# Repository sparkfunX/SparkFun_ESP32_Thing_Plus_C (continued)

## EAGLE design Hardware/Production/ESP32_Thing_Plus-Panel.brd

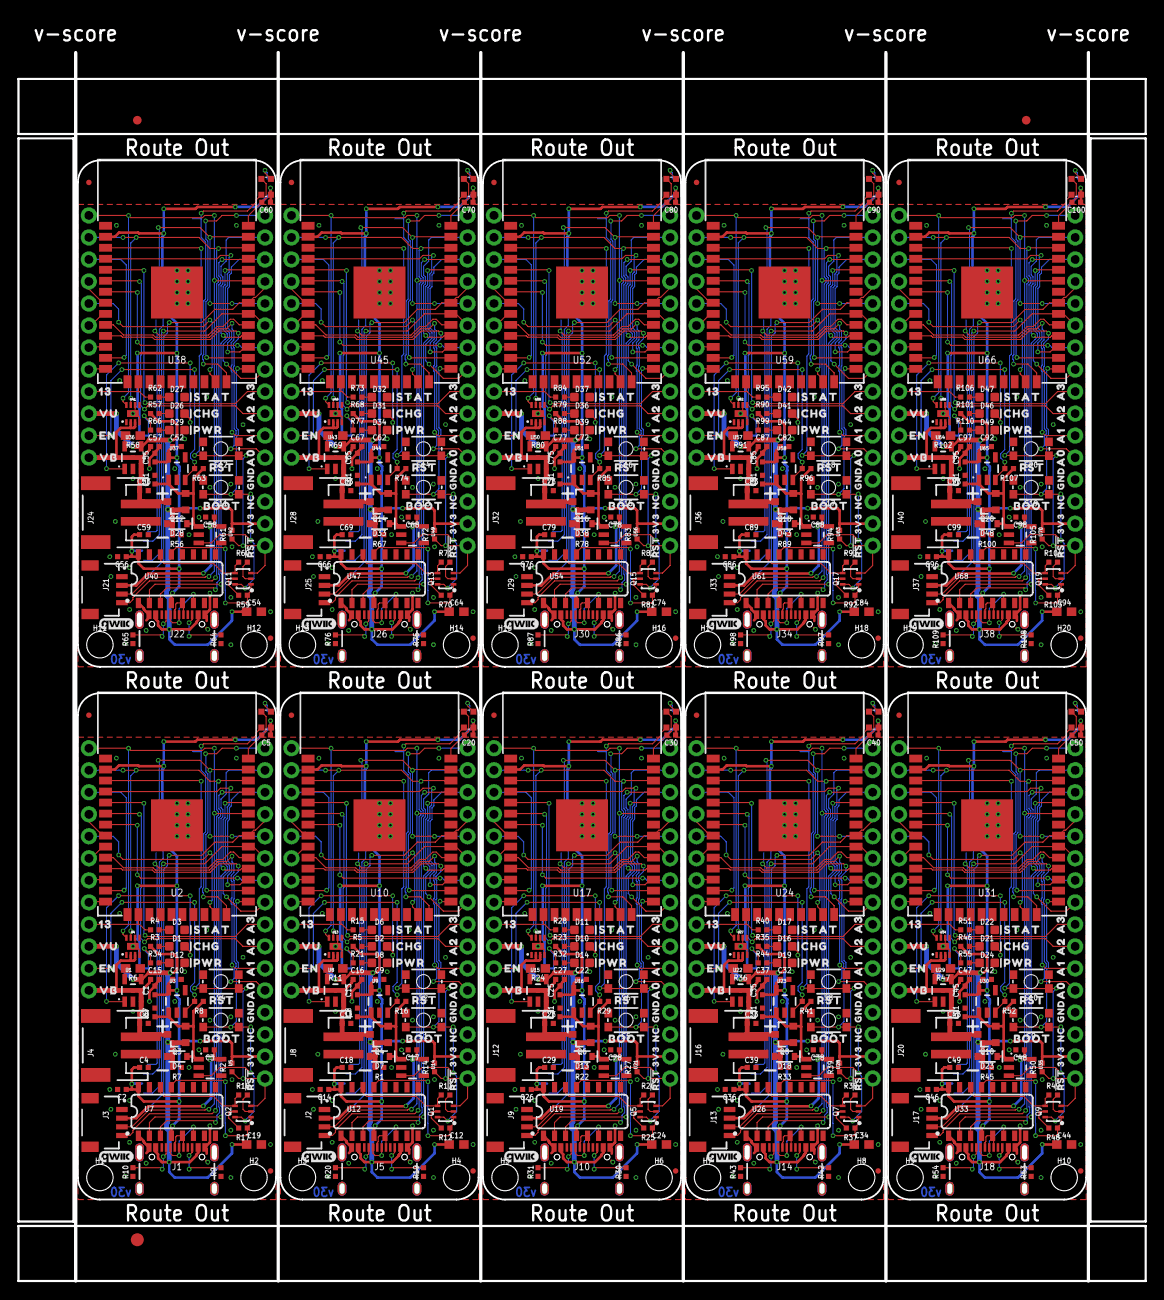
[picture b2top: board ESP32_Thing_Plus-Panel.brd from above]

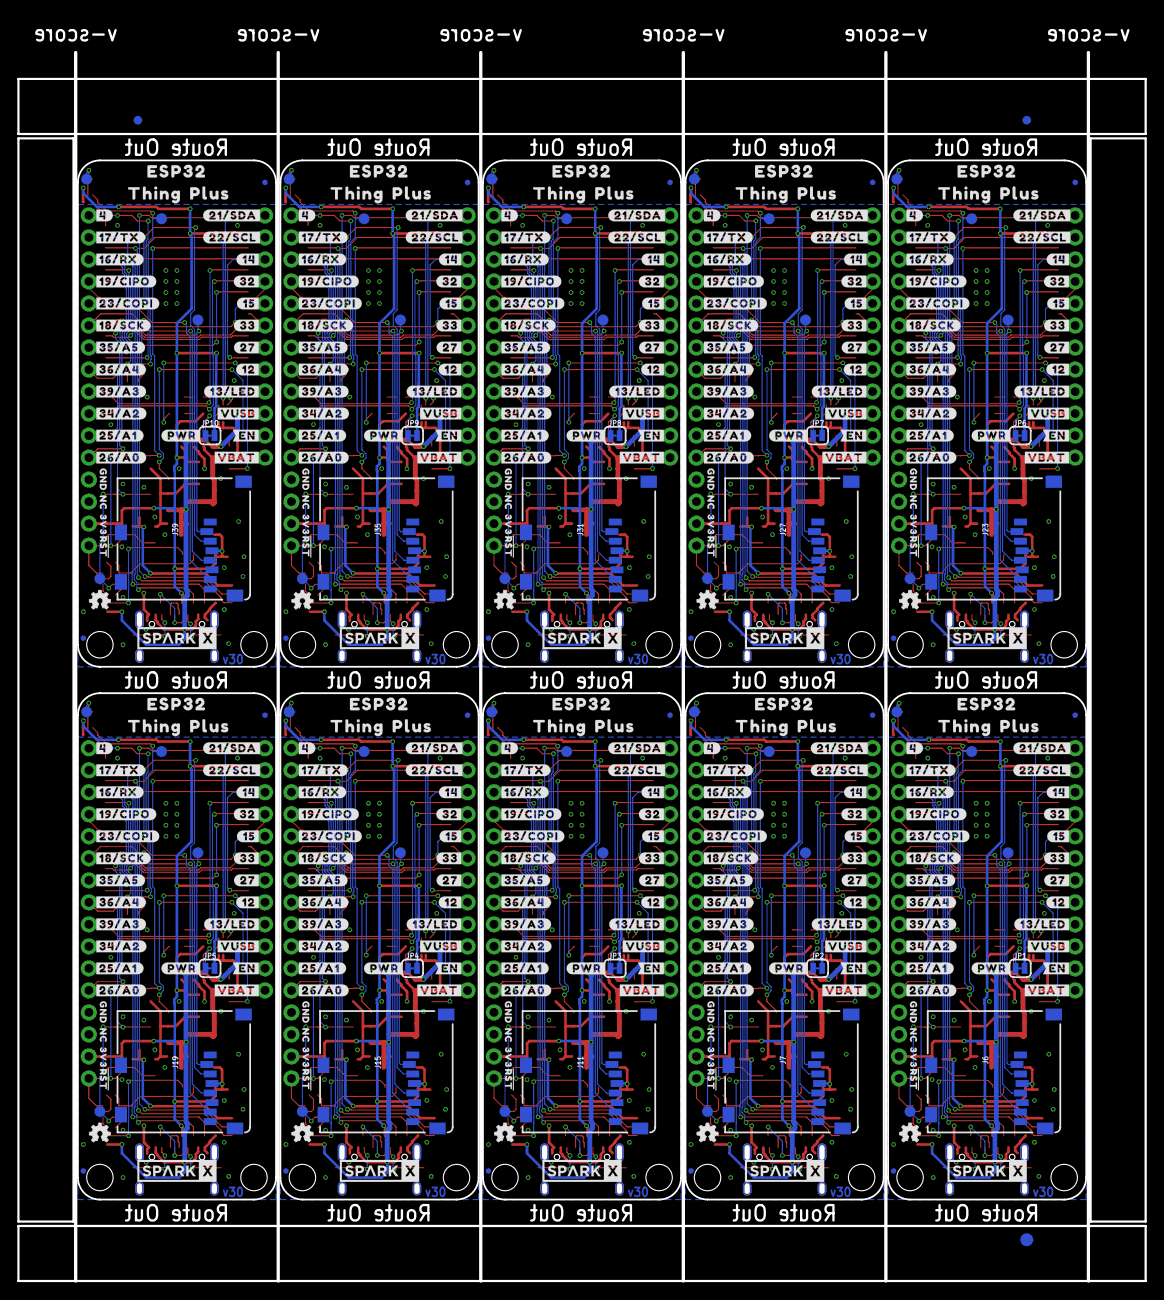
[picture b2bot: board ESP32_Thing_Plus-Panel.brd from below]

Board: 2 copper layers, 129.7 x 145.4 mm, 1046 parts (423 on the bottom side), 490 nets.

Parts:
C1, C13, C25, C35, C45, C55, C65, C75, C85, C95: 10uF; 0402-TIGHT
C2, C4, C5, C14, C15, C16, C18, C20, C26, C27, C29, C30, C36, C37, C39, C40, C46, C47, C49, C50, C56, C57, C59, C60, C66, C67, C69, C70, C76, C77, C79, C80, C86, C87, C89, C90, C96, C97, C99, C100: 0.1uF; 0402-TIGHT
C3, C7, C8, C9, C10, C17, C21, C22, C28, C31, C32, C38, C41, C42, C48, C51, C52, C58, C61, C62, C68, C71, C72, C78, C81, C82, C88, C91, C92, C98: 1.0uF; 0402-TIGHT
C6, C11, C23, C33, C43, C53, C63, C73, C83, C93: 4.7uF; 0402-TIGHT
C12, C19, C24, C34, C44, C54, C64, C74, C84, C94: 4.7uF; 0603
D1, D2, D10, D16, D21, D26, D31, D36, D41, D46: Yellow; LED-0603
D3, D6, D11, D17, D22, D27, D32, D37, D42, D47: BLUE; LED-0603
D4, D7, D13, D18, D23, D28, D33, D38, D43, D48: 3A/10V/280mV; SOD-323
D5, D9, D15, D20, D25, D30, D35, D40, D45, D50: WS2812; WS2812-2020
D8, D12, D14, D19, D24, D29, D34, D39, D44, D49: RED; LED-0603
E$1, E$2, E$3, E$4: FIDUCIAL-1X2
E$5, E$6: FIDUCIAL-1.5X3
FD1, FD2, FD3, FD4, FD5, FD6, FD7, FD8, FD9, FD10, FD11, FD12, FD13, FD14, FD15, FD16, FD17, FD18, FD19, FD20, FD21, FD22, FD23, FD24, FD25, FD26, FD27, FD28, FD29, FD30, FD31, FD32, FD33, FD34, FD35, FD36, FD37, FD38, FD39, FD40: FIDUCIALUFIDUCIAL; FIDUCIAL-MICRO
H1, H2, H3, H4, H5, H6, H7, H8, H9, H10, H11, H12, H13, H14, H15, H16, H17, H18, H19, H20: STAND-OFFTIGHT; STAND-OFF-TIGHT
J1, J5, J10, J14, J18, J22, J26, J30, J34, J38: USB-C-16P-2LAYER-PADS
J2, J3, J9, J13, J17, J21, J25, J29, J33, J37: QWIIC_RIGHT_ANGLE; JST04_1MM_RA
J4, J8, J12, J16, J20, J24, J28, J32, J36, J40: JST-2-SMD
J6, J7, J11, J15, J19, J23, J27, J31, J35, J39: microSD; MICRO-SD-SOCKET
JP1, JP2, JP3, JP4, JP5, JP6, JP7, JP8, JP9, JP10: SMT-JUMPER_2_NC_TRACE_SILK
LOGO1, LOGO2, LOGO5, LOGO7, LOGO9, LOGO11, LOGO13, LOGO15, LOGO17, LOGO19: OSHW-LOGOMINI; OSHW-LOGO-MINI
LOGO3, LOGO4, LOGO6, LOGO8, LOGO10, LOGO12, LOGO14, LOGO16, LOGO18, LOGO20: QWIIC_LOGO_4MM; QWIIC_4MM
Q1, Q2, Q5, Q7, Q9, Q11, Q13, Q15, Q17, Q19: MBT3904DW1T1; SC70-6
Q3, Q4, Q6, Q8, Q10, Q12, Q14, Q16, Q18, Q20: 20V/4.2A/52mΩ/1.4W; SOT23-3
R1, R2, R7, R8, R12, R13, R14, R16, R17, R18, R22, R25, R26, R27, R29, R33, R37, R38, R39, R41, R45, R48, R49, R50, R52, R56, R59, R60, R61, R63, R67, R70, R71, R72, R74, R78, R81, R82, R83, R85, R89, R92, R93, R94, R96, R100, R103, R104, R105, R107: 10k; 0402-TIGHT
R3, R4, R5, R15, R21, R23, R28, R32, R34, R35, R40, R44, R46, R51, R55, R57, R62, R66, R68, R73, R77, R79, R84, R88, R90, R95, R99, R101, R106, R110: 1k; 0402-TIGHT
R6, R11, R24, R36, R47, R58, R69, R80, R91, R102: 2.0k; 0603
R9, R10, R19, R20, R30, R31, R42, R43, R53, R54, R64, R65, R75, R76, R86, R87, R97, R98, R108, R109: 5.1k; 0402-TIGHT
S1, S3, S5, S7, S9, S11, S13, S15, S17, S19: Boot; TACTILE_SWITCH_SMD_4.6X2.8MM
S2, S4, S6, S8, S10, S12, S14, S16, S18, S20: Reset; TACTILE_SWITCH_SMD_4.6X2.8MM
TP1, TP2, TP3, TP4, TP5, TP6, TP7, TP8, TP9, TP10, TP11, TP12, TP13, TP14, TP15, TP16, TP17, TP18, TP19, TP20, TP21, TP22, TP23, TP24, TP25, TP26, TP27, TP28, TP29, TP30, TP31, TP32, TP33, TP34, TP35, TP36, TP37, TP38, TP39, TP40: PAD.03X.05
U1, U8, U15, U22, U29, U36, U43, U50, U57, U64: MCP73831; SOT23-5
U2, U10, U17, U24, U31, U38, U45, U52, U59, U66: ESP-WROOM-32NARROW; ESP-WROOM-32-NARROW
U3, U5, U9, U14, U16, U21, U23, U28, U30, U35, U37, U42, U44, U49, U51, U56, U58, U63, U65, U70: AP2112K-3.3; SOT23-5
U4, U13, U20, U27, U34, U41, U48, U55, U62, U69: MAX17048; DFN-8
U6, U11, U18, U25, U32, U39, U46, U53, U60, U67: THINGPLUS_LOGICAL; THINGPLUS_FOOTPRINT
U7, U12, U19, U26, U33, U40, U47, U54, U61, U68: CH340C; SO016
U$1, U$55, U$150, U$200, U$250, U$300, U$350, U$400, U$450, U$500: SPARKX-LOGO4; SPARKX-MEDIUM
U$2, U$24, U$58, U$151, U$201, U$251, U$301, U$351, U$401, U$451: CHG1
U$3, U$25, U$59, U$152, U$202, U$252, U$302, U$352, U$402, U$452: PWR2
U$4, U$26, U$60, U$153, U$203, U$253, U$303, U$353, U$403, U$453: STAT0
U$5, U$61, U$68, U$154, U$204, U$254, U$304, U$354, U$404, U$454: A03
U$6, U$63, U$69, U$155, U$205, U$255, U$305, U$355, U$405, U$455: A12
U$7, U$64, U$70, U$156, U$206, U$256, U$306, U$356, U$406, U$456: A21
U$8, U$65, U$71, U$157, U$207, U$257, U$307, U$357, U$407, U$457: A30
U$9, U$66, U$74, U$158, U$208, U$258, U$308, U$358, U$408, U$458: EN3
U$10, U$67, U$77, U$159, U$209, U$259, U$309, U$359, U$409, U$459: 130
U$11, U$78, U$110, U$160, U$210, U$260, U$310, U$360, U$410, U$460: BOOT0
U$12, U$50, U$79, U$109, U$111, U$145, U$161, U$195, U$211, U$245, U$261, U$295, U$311, U$345, U$361, U$395, U$411, U$445, U$461, U$495: #RST#0
U$13, U$80, U$112, U$162, U$212, U$262, U$312, U$362, U$412, U$462: RST0
U$14, U$73, U$113, U$163, U$213, U$263, U$313, U$363, U$413, U$463: VB1
U$15, U$76, U$114, U$164, U$214, U$264, U$314, U$364, U$414, U$464: VU0
U$16, U$23, U$49, U$108, U$115, U$144, U$165, U$194, U$215, U$244, U$265, U$294, U$315, U$344, U$365, U$394, U$415, U$444, U$465, U$494: 3V30
U$17, U$57, U$116, U$166, U$216, U$266, U$316, U$366, U$416, U$466: #4#0
U$18, U$62, U$117, U$167, U$217, U$267, U$317, U$367, U$417, U$467: #23#COPI#0
U$19, U$72, U$118, U$168, U$218, U$268, U$318, U$368, U$418, U$468: #17#TX#0
U$20, U$81, U$119, U$169, U$219, U$269, U$319, U$369, U$419, U$469: #16#RX#0
U$21, U$82, U$120, U$170, U$220, U$270, U$320, U$370, U$420, U$470: #19#CIPO#0
U$22, U$83, U$121, U$171, U$221, U$271, U$321, U$371, U$421, U$471: #18#SCK#0
U$27, U$84, U$122, U$172, U$222, U$272, U$322, U$372, U$422, U$472: #35#A5#0
U$28, U$85, U$123, U$173, U$223, U$273, U$323, U$373, U$423, U$473: #36#A4#0
U$29, U$86, U$124, U$174, U$224, U$274, U$324, U$374, U$424, U$474: #25#A1#2
U$30, U$87, U$125, U$175, U$225, U$275, U$325, U$375, U$425, U$475: #26#A0#3
U$31, U$88, U$126, U$176, U$226, U$276, U$326, U$376, U$426, U$476: #34#A2#1
U$32, U$89, U$127, U$177, U$227, U$277, U$327, U$377, U$427, U$477: #39#A3#0
U$33, U$90, U$128, U$178, U$228, U$278, U$328, U$378, U$428, U$478: #12#4
U$34, U$91, U$129, U$179, U$229, U$279, U$329, U$379, U$429, U$479: #14#9
U$35, U$92, U$130, U$180, U$230, U$280, U$330, U$380, U$430, U$480: #15#7
U$36, U$93, U$131, U$181, U$231, U$281, U$331, U$381, U$431, U$481: #27#5
U$37, U$94, U$132, U$182, U$232, U$282, U$332, U$382, U$432, U$482: #32#8
U$38, U$95, U$133, U$183, U$233, U$283, U$333, U$383, U$433, U$483: #33#6
U$39, U$96, U$134, U$184, U$234, U$284, U$334, U$384, U$434, U$484: #EN#1
U$40, U$97, U$135, U$185, U$235, U$285, U$335, U$385, U$435, U$485: #VBAT#0
U$41, U$98, U$136, U$186, U$236, U$286, U$336, U$386, U$436, U$486: #VUSB#2
U$42, U$99, U$137, U$187, U$237, U$287, U$337, U$387, U$437, U$487: #13#LED#0
U$43, U$100, U$138, U$188, U$238, U$288, U$338, U$388, U$438, U$488: #21#SDA#1
U$44, U$101, U$139, U$189, U$239, U$289, U$339, U$389, U$439, U$489: #22#SCL#0
U$45, U$102, U$140, U$190, U$240, U$290, U$340, U$390, U$440, U$490: #PWR#0
U$46, U$103, U$141, U$191, U$241, U$291, U$341, U$391, U$441, U$491: ESP320
U$47, U$104, U$142, U$192, U$242, U$292, U$342, U$392, U$442, U$492: THING1
U$48, U$105, U$143, U$193, U$243, U$293, U$343, U$393, U$443, U$493: PLUS2
U$51, U$52, U$56, U$75, U$146, U$147, U$196, U$197, U$246, U$247, U$296, U$297, U$346, U$347, U$396, U$397, U$446, U$447, U$496, U$497: GND1
U$53, U$54, U$106, U$107, U$148, U$149, U$198, U$199, U$248, U$249, U$298, U$299, U$348, U$349, U$398, U$399, U$448, U$449, U$498, U$499: NC0

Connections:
3.3V: C1.1, C2.1, C4.1, C5.1, C10.1, D5.VCC, J6.VCC, JP1.2, R2.2, U2.2, U3.5, U6.3V3, U7.4, U7.16
3.3V1: C9.1, C13.1, C14.1, C18.1, C20.1, D9.VCC, J7.VCC, JP2.2, R14.2, U9.5, U10.2, U11.3V3, U12.4, U12.16
3.3V2: C22.1, C25.1, C26.1, C29.1, C30.1, D15.VCC, J11.VCC, JP3.2, R27.2, U16.5, U17.2, U18.3V3, U19.4, U19.16
3.3V3: C32.1, C35.1, C36.1, C39.1, C40.1, D20.VCC, J15.VCC, JP4.2, R39.2, U23.5, U24.2, U25.3V3, U26.4, U26.16
3.3V4: C42.1, C45.1, C46.1, C49.1, C50.1, D25.VCC, J19.VCC, JP5.2, R50.2, U30.5, U31.2, U32.3V3, U33.4, U33.16
3.3V5: C52.1, C55.1, C56.1, C59.1, C60.1, D30.VCC, J23.VCC, JP6.2, R61.2, U37.5, U38.2, U39.3V3, U40.4, U40.16
3.3V6: C62.1, C65.1, C66.1, C69.1, C70.1, D35.VCC, J27.VCC, JP7.2, R72.2, U44.5, U45.2, U46.3V3, U47.4, U47.16
3.3V7: C72.1, C75.1, C76.1, C79.1, C80.1, D40.VCC, J31.VCC, JP8.2, R83.2, U51.5, U52.2, U53.3V3, U54.4, U54.16
3.3V8: C82.1, C85.1, C86.1, C89.1, C90.1, D45.VCC, J35.VCC, JP9.2, R94.2, U58.5, U59.2, U60.3V3, U61.4, U61.16
3.3V9: C92.1, C95.1, C96.1, C99.1, C100.1, D50.VCC, J39.VCC, JP10.2, R105.2, U65.5, U66.2, U67.3V3, U68.4, U68.16
!RESET!: Q2.3, R2.1, S4.3, S4.4, U2.3, U6.RST
!RESET!1: Q1.3, R14.1, S2.3, S2.4, U10.3, U11.RST
!RESET!2: Q5.3, R27.1, S6.3, S6.4, U17.3, U18.RST
!RESET!3: Q7.3, R39.1, S8.3, S8.4, U24.3, U25.RST
!RESET!4: Q9.3, R50.1, S10.3, S10.4, U31.3, U32.RST
!RESET!5: Q11.3, R61.1, S12.3, S12.4, U38.3, U39.RST
!RESET!6: Q13.3, R72.1, S14.3, S14.4, U45.3, U46.RST
!RESET!7: Q15.3, R83.1, S16.3, S16.4, U52.3, U53.RST
!RESET!8: Q17.3, R94.1, S18.3, S18.4, U59.3, U60.RST
!RESET!9: Q19.3, R105.1, S20.3, S20.4, U66.3, U67.RST
CH340-DTR: Q2.1, R17.1, U7.13
CH340-DTR1: Q1.1, R12.1, U12.13
CH340-DTR2: Q5.1, R25.1, U19.13
CH340-DTR3: Q7.1, R37.1, U26.13
CH340-DTR4: Q9.1, R48.1, U33.13
CH340-DTR5: Q11.1, R59.1, U40.13
CH340-DTR6: Q13.1, R70.1, U47.13
CH340-DTR7: Q15.1, R81.1, U54.13
CH340-DTR8: Q17.1, R92.1, U61.13
CH340-DTR9: Q19.1, R103.1, U68.13
CH340-RTS: Q2.4, R18.1, U7.14
CH340-RTS1: Q1.4, R13.1, U12.14
CH340-RTS2: Q5.4, R26.1, U19.14
CH340-RTS3: Q7.4, R38.1, U26.14
CH340-RTS4: Q9.4, R49.1, U33.14
CH340-RTS5: Q11.4, R60.1, U40.14
CH340-RTS6: Q13.4, R71.1, U47.14
CH340-RTS7: Q15.4, R82.1, U54.14
CH340-RTS8: Q17.4, R93.1, U61.14
CH340-RTS9: Q19.4, R104.1, U68.14
CH340-RX: U2.35, U7.3
CH340-RX1: U10.35, U12.3
CH340-RX2: U17.35, U19.3
CH340-RX3: U24.35, U26.3
CH340-RX4: U31.35, U33.3
CH340-RX5: U38.35, U40.3
CH340-RX6: U45.35, U47.3
CH340-RX7: U52.35, U54.3
CH340-RX8: U59.35, U61.3
CH340-RX9: U66.35, U68.3
CH340-TX: U2.34, U7.2
CH340-TX1: U10.34, U12.2
CH340-TX2: U17.34, U19.2
CH340-TX3: U24.34, U26.2
CH340-TX4: U31.34, U33.2
CH340-TX5: U38.34, U40.2
CH340-TX6: U45.34, U47.2
CH340-TX7: U52.34, U54.2
CH340-TX8: U59.34, U61.2
CH340-TX9: U66.34, U68.2
CHG: D1.C, U1.1
CHG1: D2.C, U8.1
CHG2: D10.C, U15.1
CHG3: D16.C, U22.1
CHG4: D21.C, U29.1
CHG5: D26.C, U36.1
CHG6: D31.C, U43.1
CHG7: D36.C, U50.1
CHG8: D41.C, U57.1
CHG9: D46.C, U64.1
CHG_LED: D1.A, R3.2
CHG_LED1: D2.A, R5.2
CHG_LED2: D10.A, R23.2
CHG_LED3: D16.A, R35.2
CHG_LED4: D21.A, R46.2
CHG_LED5: D26.A, R57.2
CHG_LED6: D31.A, R68.2
CHG_LED7: D36.A, R79.2
CHG_LED8: D41.A, R90.2
CHG_LED9: D46.A, R101.2
D+: J1.A6, J1.B6, U7.5
D+1: J5.A6, J5.B6, U12.5
D+2: J10.A6, J10.B6, U19.5
D+3: J14.A6, J14.B6, U26.5
D+4: J18.A6, J18.B6, U33.5
D+5: J22.A6, J22.B6, U40.5
D+6: J26.A6, J26.B6, U47.5
D+7: J30.A6, J30.B6, U54.5
D+8: J34.A6, J34.B6, U61.5
D+9: J38.A6, J38.B6, U68.5
D-: J1.A7, J1.B7, U7.6
D-1: J5.A7, J5.B7, U12.6
D-2: J10.A7, J10.B7, U19.6
D-3: J14.A7, J14.B7, U26.6
D-4: J18.A7, J18.B7, U33.6
D-5: J22.A7, J22.B7, U40.6
D-6: J26.A7, J26.B7, U47.6
D-7: J30.A7, J30.B7, U54.6
D-8: J34.A7, J34.B7, U61.6
D-9: J38.A7, J38.B7, U68.6
DTR-10K: Q2.5, R17.2
DTR-10K1: Q1.5, R12.2
DTR-10K2: Q5.5, R25.2
DTR-10K3: Q7.5, R37.2
DTR-10K4: Q9.5, R48.2
DTR-10K5: Q11.5, R59.2
DTR-10K6: Q13.5, R70.2
DTR-10K7: Q15.5, R81.2
DTR-10K8: Q17.5, R92.2
DTR-10K9: Q19.5, R103.2
ESP_0/QPWR: Q2.6, S3.3, S3.4, TP1.P$1, U2.25, U5.3
ESP_0/QPWR1: Q1.6, S1.3, S1.4, TP5.P$1, U10.25, U14.3
ESP_0/QPWR2: Q5.6, S5.3, S5.4, TP9.P$1, U17.25, U21.3
ESP_0/QPWR3: Q7.6, S7.3, S7.4, TP13.P$1, U24.25, U28.3
ESP_0/QPWR4: Q9.6, S9.3, S9.4, TP17.P$1, U31.25, U35.3
ESP_0/QPWR5: Q11.6, S11.3, S11.4, TP21.P$1, U38.25, U42.3
ESP_0/QPWR6: Q13.6, S13.3, S13.4, TP25.P$1, U45.25, U49.3
ESP_0/QPWR7: Q15.6, S15.3, S15.4, TP29.P$1, U52.25, U56.3
ESP_0/QPWR8: Q17.6, S17.3, S17.4, TP33.P$1, U59.25, U63.3
ESP_0/QPWR9: Q19.6, S19.3, S19.4, TP37.P$1, U66.25, U70.3
ESP_2/RGB_DI: D5.DI, TP3.P$1, U2.24
ESP_2/RGB_DI1: D9.DI, TP7.P$1, U10.24
ESP_2/RGB_DI2: D15.DI, TP11.P$1, U17.24
ESP_2/RGB_DI3: D20.DI, TP15.P$1, U24.24
ESP_2/RGB_DI4: D25.DI, TP19.P$1, U31.24
ESP_2/RGB_DI5: D30.DI, TP23.P$1, U38.24
ESP_2/RGB_DI6: D35.DI, TP27.P$1, U45.24
ESP_2/RGB_DI7: D40.DI, TP31.P$1, U52.24
ESP_2/RGB_DI8: D45.DI, TP35.P$1, U59.24
ESP_2/RGB_DI9: D50.DI, TP39.P$1, U66.24
ESP_4/TP_FB: U2.26, U6.FREEBIE
ESP_4/TP_FB1: U10.26, U11.FREEBIE
ESP_4/TP_FB2: U17.26, U18.FREEBIE
ESP_4/TP_FB3: U24.26, U25.FREEBIE
ESP_4/TP_FB4: U31.26, U32.FREEBIE
ESP_4/TP_FB5: U38.26, U39.FREEBIE
ESP_4/TP_FB6: U45.26, U46.FREEBIE
ESP_4/TP_FB7: U52.26, U53.FREEBIE
ESP_4/TP_FB8: U59.26, U60.FREEBIE
ESP_4/TP_FB9: U66.26, U67.FREEBIE
ESP_5/SD_CS: J6.CS/DAT3, TP4.P$1, U2.29
ESP_5/SD_CS1: J7.CS/DAT3, TP8.P$1, U10.29
ESP_5/SD_CS2: J11.CS/DAT3, TP12.P$1, U17.29
ESP_5/SD_CS3: J15.CS/DAT3, TP16.P$1, U24.29
ESP_5/SD_CS4: J19.CS/DAT3, TP20.P$1, U31.29
ESP_5/SD_CS5: J23.CS/DAT3, TP24.P$1, U38.29
ESP_5/SD_CS6: J27.CS/DAT3, TP28.P$1, U45.29
ESP_5/SD_CS7: J31.CS/DAT3, TP32.P$1, U52.29
ESP_5/SD_CS8: J35.CS/DAT3, TP36.P$1, U59.29
ESP_5/SD_CS9: J39.CS/DAT3, TP40.P$1, U66.29
ESP_12/TP_1: U10.14, U11.12
ESP_12/TP_2: U17.14, U18.12
ESP_12/TP_3: U24.14, U25.12
ESP_12/TP_4: U31.14, U32.12
ESP_12/TP_5: U38.14, U39.12
ESP_12/TP_6: U45.14, U46.12
ESP_12/TP_7: U52.14, U53.12
ESP_12/TP_8: U59.14, U60.12
ESP_12/TP_9: U66.14, U67.12
ESP_12/TP_12: U2.14, U6.12
ESP_13/TP_13/LED: R4.1, U2.16, U6.13
ESP_13/TP_13/LED1: R15.1, U10.16, U11.13
ESP_13/TP_13/LED2: R28.1, U17.16, U18.13
ESP_13/TP_13/LED3: R40.1, U24.16, U25.13
ESP_13/TP_13/LED4: R51.1, U31.16, U32.13
ESP_13/TP_13/LED5: R62.1, U38.16, U39.13
ESP_13/TP_13/LED6: R73.1, U45.16, U46.13
ESP_13/TP_13/LED7: R84.1, U52.16, U53.13
ESP_13/TP_13/LED8: R95.1, U59.16, U60.13
ESP_13/TP_13/LED9: R106.1, U66.16, U67.13
ESP_14/TP_1: U10.13, U11.7
ESP_14/TP_2: U17.13, U18.7
ESP_14/TP_3: U24.13, U25.7
ESP_14/TP_4: U31.13, U32.7
ESP_14/TP_5: U38.13, U39.7
ESP_14/TP_6: U45.13, U46.7
ESP_14/TP_7: U2.13, U6.7
ESP_14/TP_8: U52.13, U53.7
ESP_14/TP_9: U59.13, U60.7
ESP_14/TP_10: U66.13, U67.7
ESP_15/TP_1: U10.23, U11.9
ESP_15/TP_2: U17.23, U18.9
ESP_15/TP_3: U24.23, U25.9
ESP_15/TP_4: U31.23, U32.9
ESP_15/TP_5: U38.23, U39.9
ESP_15/TP_6: U45.23, U46.9
ESP_15/TP_7: U52.23, U53.9
ESP_15/TP_8: U59.23, U60.9
ESP_15/TP_9: U2.23, U6.9
ESP_15/TP_10: U66.23, U67.9
ESP_16/TP_RX: U2.27, U6.RX
ESP_16/TP_RX1: U10.27, U11.RX
ESP_16/TP_RX2: U17.27, U18.RX
ESP_16/TP_RX3: U24.27, U25.RX
ESP_16/TP_RX4: U31.27, U32.RX
ESP_16/TP_RX5: U38.27, U39.RX
ESP_16/TP_RX6: U45.27, U46.RX
ESP_16/TP_RX7: U52.27, U53.RX
ESP_16/TP_RX8: U59.27, U60.RX
ESP_16/TP_RX9: U66.27, U67.RX
ESP_17/TP_TX: U2.28, U6.TX
ESP_17/TP_TX1: U10.28, U11.TX
ESP_17/TP_TX2: U17.28, U18.TX
ESP_17/TP_TX3: U24.28, U25.TX
ESP_17/TP_TX4: U31.28, U32.TX
ESP_17/TP_TX5: U38.28, U39.TX
ESP_17/TP_TX6: U45.28, U46.TX
ESP_17/TP_TX7: U52.28, U53.TX
ESP_17/TP_TX8: U59.28, U60.TX
ESP_17/TP_TX9: U66.28, U67.TX
ESP_18/TP_SCK: J6.SCLK, U2.30, U6.SCK
ESP_18/TP_SCK1: J7.SCLK, U10.30, U11.SCK
ESP_18/TP_SCK2: J11.SCLK, U17.30, U18.SCK
ESP_18/TP_SCK3: J15.SCLK, U24.30, U25.SCK
ESP_18/TP_SCK4: J19.SCLK, U31.30, U32.SCK
ESP_18/TP_SCK5: J23.SCLK, U38.30, U39.SCK
ESP_18/TP_SCK6: J27.SCLK, U45.30, U46.SCK
ESP_18/TP_SCK7: J31.SCLK, U52.30, U53.SCK
ESP_18/TP_SCK8: J35.SCLK, U59.30, U60.SCK
ESP_18/TP_SCK9: J39.SCLK, U66.30, U67.SCK
ESP_19/TP_CIPO: J6.DO/DAT0, U2.31, U6.CIPO
ESP_19/TP_CIPO1: J7.DO/DAT0, U10.31, U11.CIPO
ESP_19/TP_CIPO2: J11.DO/DAT0, U17.31, U18.CIPO
ESP_19/TP_CIPO3: J15.DO/DAT0, U24.31, U25.CIPO
ESP_19/TP_CIPO4: J19.DO/DAT0, U31.31, U32.CIPO
ESP_19/TP_CIPO5: J23.DO/DAT0, U38.31, U39.CIPO
ESP_19/TP_CIPO6: J27.DO/DAT0, U45.31, U46.CIPO
ESP_19/TP_CIPO7: J31.DO/DAT0, U52.31, U53.CIPO
ESP_19/TP_CIPO8: J35.DO/DAT0, U59.31, U60.CIPO
ESP_19/TP_CIPO9: J39.DO/DAT0, U66.31, U67.CIPO
ESP_21/TP_SDA: J3.3, U2.33, U4.8, U6.SDA
ESP_21/TP_SDA1: J2.3, U10.33, U11.SDA, U13.8
ESP_21/TP_SDA2: J9.3, U17.33, U18.SDA, U20.8
ESP_21/TP_SDA3: J13.3, U24.33, U25.SDA, U27.8
ESP_21/TP_SDA4: J17.3, U31.33, U32.SDA, U34.8
ESP_21/TP_SDA5: J21.3, U38.33, U39.SDA, U41.8
ESP_21/TP_SDA6: J25.3, U45.33, U46.SDA, U48.8
ESP_21/TP_SDA7: J29.3, U52.33, U53.SDA, U55.8
ESP_21/TP_SDA8: J33.3, U59.33, U60.SDA, U62.8
ESP_21/TP_SDA9: J37.3, U66.33, U67.SDA, U69.8
ESP_22/TP_SCL: J3.4, U2.36, U4.7, U6.SCL
ESP_22/TP_SCL1: J2.4, U10.36, U11.SCL, U13.7
ESP_22/TP_SCL2: J9.4, U17.36, U18.SCL, U20.7
ESP_22/TP_SCL3: J13.4, U24.36, U25.SCL, U27.7
ESP_22/TP_SCL4: J17.4, U31.36, U32.SCL, U34.7
ESP_22/TP_SCL5: J21.4, U38.36, U39.SCL, U41.7
ESP_22/TP_SCL6: J25.4, U45.36, U46.SCL, U48.7
ESP_22/TP_SCL7: J29.4, U52.36, U53.SCL, U55.7
ESP_22/TP_SCL8: J33.4, U59.36, U60.SCL, U62.7
ESP_22/TP_SCL9: J37.4, U66.36, U67.SCL, U69.7
ESP_23/TP_COPI: J6.DI/CMD, U2.37, U6.COPI
ESP_23/TP_COPI1: J7.DI/CMD, U10.37, U11.COPI
ESP_23/TP_COPI2: J11.DI/CMD, U17.37, U18.COPI
ESP_23/TP_COPI3: J15.DI/CMD, U24.37, U25.COPI
ESP_23/TP_COPI4: J19.DI/CMD, U31.37, U32.COPI
ESP_23/TP_COPI5: J23.DI/CMD, U38.37, U39.COPI
ESP_23/TP_COPI6: J27.DI/CMD, U45.37, U46.COPI
ESP_23/TP_COPI7: J31.DI/CMD, U52.37, U53.COPI
ESP_23/TP_COPI8: J35.DI/CMD, U59.37, U60.COPI
ESP_23/TP_COPI9: J39.DI/CMD, U66.37, U67.COPI
ESP_25/TP_A1: U2.10, U6.A1
ESP_25/TP_A2: U10.10, U11.A1
ESP_25/TP_A3: U17.10, U18.A1
ESP_25/TP_A4: U24.10, U25.A1
ESP_25/TP_A5: U31.10, U32.A1
ESP_25/TP_A6: U38.10, U39.A1
ESP_25/TP_A7: U45.10, U46.A1
ESP_25/TP_A8: U52.10, U53.A1
ESP_25/TP_A9: U59.10, U60.A1
ESP_25/TP_A10: U66.10, U67.A1
ESP_26/TP_A0: U2.11, U6.A0
ESP_26/TP_A1: U10.11, U11.A0
ESP_26/TP_A2: U17.11, U18.A0
ESP_26/TP_A3: U24.11, U25.A0
ESP_26/TP_A4: U31.11, U32.A0
ESP_26/TP_A5: U38.11, U39.A0
ESP_26/TP_A6: U45.11, U46.A0
ESP_26/TP_A7: U52.11, U53.A0
ESP_26/TP_A8: U59.11, U60.A0
ESP_26/TP_A9: U66.11, U67.A0
ESP_27/TP_1: U10.12, U11.11
ESP_27/TP_2: U17.12, U18.11
ESP_27/TP_3: U24.12, U25.11
ESP_27/TP_4: U31.12, U32.11
ESP_27/TP_5: U38.12, U39.11
ESP_27/TP_6: U45.12, U46.11
ESP_27/TP_7: U52.12, U53.11
ESP_27/TP_8: U59.12, U60.11
ESP_27/TP_9: U66.12, U67.11
ESP_27/TP_11: U2.12, U6.11
ESP_32/TP_1: U10.8, U11.8
ESP_32/TP_2: U17.8, U18.8
ESP_32/TP_3: U24.8, U25.8
ESP_32/TP_4: U31.8, U32.8
ESP_32/TP_5: U38.8, U39.8
ESP_32/TP_6: U45.8, U46.8
ESP_32/TP_7: U52.8, U53.8
ESP_32/TP_8: U2.8, U6.8
ESP_32/TP_9: U59.8, U60.8
ESP_32/TP_10: U66.8, U67.8
ESP_33/TP_1: U10.9, U11.10
ESP_33/TP_2: U17.9, U18.10
ESP_33/TP_3: U24.9, U25.10
ESP_33/TP_4: U31.9, U32.10
ESP_33/TP_5: U38.9, U39.10
ESP_33/TP_6: U45.9, U46.10
ESP_33/TP_7: U52.9, U53.10
ESP_33/TP_8: U59.9, U60.10
ESP_33/TP_9: U66.9, U67.10
ESP_33/TP_10: U2.9, U6.10
ESP_34/TP_A1: U10.6, U11.A2
ESP_34/TP_A2: U2.6, U6.A2
ESP_34/TP_A3: U17.6, U18.A2
ESP_34/TP_A4: U24.6, U25.A2
ESP_34/TP_A5: U31.6, U32.A2
ESP_34/TP_A6: U38.6, U39.A2
ESP_34/TP_A7: U45.6, U46.A2
ESP_34/TP_A8: U52.6, U53.A2
ESP_34/TP_A9: U59.6, U60.A2
ESP_34/TP_A10: U66.6, U67.A2
ESP_35/TP_A1: U10.7, U11.A5
ESP_35/TP_A2: U17.7, U18.A5
ESP_35/TP_A3: U24.7, U25.A5
ESP_35/TP_A4: U31.7, U32.A5
ESP_35/TP_A5: U2.7, U6.A5
ESP_35/TP_A6: U38.7, U39.A5
ESP_35/TP_A7: U45.7, U46.A5
ESP_35/TP_A8: U52.7, U53.A5
ESP_35/TP_A9: U59.7, U60.A5
ESP_35/TP_A10: U66.7, U67.A5
ESP_36/TP_A1: U10.4, U11.A4
ESP_36/TP_A2: U17.4, U18.A4
ESP_36/TP_A3: U24.4, U25.A4
ESP_36/TP_A4: U2.4, U6.A4
ESP_36/TP_A5: U31.4, U32.A4
ESP_36/TP_A6: U38.4, U39.A4
ESP_36/TP_A7: U45.4, U46.A4
ESP_36/TP_A8: U52.4, U53.A4
ESP_36/TP_A9: U59.4, U60.A4
ESP_36/TP_A10: U66.4, U67.A4
ESP_39/TP_A1: U10.5, U11.A3
ESP_39/TP_A2: U17.5, U18.A3
ESP_39/TP_A3: U2.5, U6.A3
ESP_39/TP_A4: U24.5, U25.A3
ESP_39/TP_A5: U31.5, U32.A3
ESP_39/TP_A6: U38.5, U39.A3
ESP_39/TP_A7: U45.5, U46.A3
ESP_39/TP_A8: U52.5, U53.A3
ESP_39/TP_A9: U59.5, U60.A3
ESP_39/TP_A10: U66.5, U67.A3
GND: C1.2, C2.2, C3.2, C4.2, C5.2, C6.2, C7.2, C10.2, C15.2, C19.2, D3.C, D5.GND, D12.C, J1.GND, J1.GND2, J3.1, J4.1, J6.CD1, J6.GND, J6.GND1, J6.GND3, R6.1, R7.1, R9.1, R10.1, S3.1, S3.2, S4.1, S4.2, U1.2, U2.1, U2.15, U2.38, U2.GND, U3.2, U4.1, U4.4, U4.6, U4.9, U5.2, U6.GND, U7.1
GND1: C8.2, C9.2, C11.2, C12.2, C13.2, C14.2, C16.2, C17.2, C18.2, C20.2, D6.C, D8.C, D9.GND, J2.1, J5.GND, J5.GND2, J7.CD1, J7.GND, J7.GND1, J7.GND3, J8.1, R1.1, R11.1, R19.1, R20.1, S1.1, S1.2, S2.1, S2.2, U8.2, U9.2, U10.1, U10.15, U10.38, U10.GND, U11.GND, U12.1, U13.1, U13.4, U13.6, U13.9, U14.2
GND2: C21.2, C22.2, C23.2, C24.2, C25.2, C26.2, C27.2, C28.2, C29.2, C30.2, D11.C, D14.C, D15.GND, J9.1, J10.GND, J10.GND2, J11.CD1, J11.GND, J11.GND1, J11.GND3, J12.1, R22.1, R24.1, R30.1, R31.1, S5.1, S5.2, S6.1, S6.2, U15.2, U16.2, U17.1, U17.15, U17.38, U17.GND, U18.GND, U19.1, U20.1, U20.4, U20.6, U20.9, U21.2
GND3: C31.2, C32.2, C33.2, C34.2, C35.2, C36.2, C37.2, C38.2, C39.2, C40.2, D17.C, D19.C, D20.GND, J13.1, J14.GND, J14.GND2, J15.CD1, J15.GND, J15.GND1, J15.GND3, J16.1, R33.1, R36.1, R42.1, R43.1, S7.1, S7.2, S8.1, S8.2, U22.2, U23.2, U24.1, U24.15, U24.38, U24.GND, U25.GND, U26.1, U27.1, U27.4, U27.6, U27.9, U28.2
GND4: C41.2, C42.2, C43.2, C44.2, C45.2, C46.2, C47.2, C48.2, C49.2, C50.2, D22.C, D24.C, D25.GND, J17.1, J18.GND, J18.GND2, J19.CD1, J19.GND, J19.GND1, J19.GND3, J20.1, R45.1, R47.1, R53.1, R54.1, S9.1, S9.2, S10.1, S10.2, U29.2, U30.2, U31.1, U31.15, U31.38, U31.GND, U32.GND, U33.1, U34.1, U34.4, U34.6, U34.9, U35.2
GND5: C51.2, C52.2, C53.2, C54.2, C55.2, C56.2, C57.2, C58.2, C59.2, C60.2, D27.C, D29.C, D30.GND, J21.1, J22.GND, J22.GND2, J23.CD1, J23.GND, J23.GND1, J23.GND3, J24.1, R56.1, R58.1, R64.1, R65.1, S11.1, S11.2, S12.1, S12.2, U36.2, U37.2, U38.1, U38.15, U38.38, U38.GND, U39.GND, U40.1, U41.1, U41.4, U41.6, U41.9, U42.2
GND6: C61.2, C62.2, C63.2, C64.2, C65.2, C66.2, C67.2, C68.2, C69.2, C70.2, D32.C, D34.C, D35.GND, J25.1, J26.GND, J26.GND2, J27.CD1, J27.GND, J27.GND1, J27.GND3, J28.1, R67.1, R69.1, R75.1, R76.1, S13.1, S13.2, S14.1, S14.2, U43.2, U44.2, U45.1, U45.15, U45.38, U45.GND, U46.GND, U47.1, U48.1, U48.4, U48.6, U48.9, U49.2
GND7: C71.2, C72.2, C73.2, C74.2, C75.2, C76.2, C77.2, C78.2, C79.2, C80.2, D37.C, D39.C, D40.GND, J29.1, J30.GND, J30.GND2, J31.CD1, J31.GND, J31.GND1, J31.GND3, J32.1, R78.1, R80.1, R86.1, R87.1, S15.1, S15.2, S16.1, S16.2, U50.2, U51.2, U52.1, U52.15, U52.38, U52.GND, U53.GND, U54.1, U55.1, U55.4, U55.6, U55.9, U56.2
GND8: C81.2, C82.2, C83.2, C84.2, C85.2, C86.2, C87.2, C88.2, C89.2, C90.2, D42.C, D44.C, D45.GND, J33.1, J34.GND, J34.GND2, J35.CD1, J35.GND, J35.GND1, J35.GND3, J36.1, R89.1, R91.1, R97.1, R98.1, S17.1, S17.2, S18.1, S18.2, U57.2, U58.2, U59.1, U59.15, U59.38, U59.GND, U60.GND, U61.1, U62.1, U62.4, U62.6, U62.9, U63.2
GND9: C91.2, C92.2, C93.2, C94.2, C95.2, C96.2, C97.2, C98.2, C99.2, C100.2, D47.C, D49.C, D50.GND, J37.1, J38.GND, J38.GND2, J39.CD1, J39.GND, J39.GND1, J39.GND3, J40.1, R100.1, R102.1, R108.1, R109.1, S19.1, S19.2, S20.1, S20.2, U64.2, U65.2, U66.1, U66.15, U66.38, U66.GND, U67.GND, U68.1, U69.1, U69.4, U69.6, U69.9, U70.2
unnamed: JP1.1, R34.1
unnamed: D3.A, R4.2
unnamed: D5.DO, TP2.P$1
unnamed: R11.2, U8.5
unnamed: J1.B5, R9.2
unnamed: J1.A5, R10.2
unnamed: D6.A, R15.2
unnamed: J5.B5, R19.2
unnamed: J5.A5, R20.2
unnamed: D8.A, R21.2
unnamed: JP2.1, R21.1
unnamed: D9.DO, TP6.P$1
unnamed: R24.2, U15.5
unnamed: R6.2, U1.5
unnamed: D11.A, R28.2
unnamed: J10.B5, R30.2
unnamed: J10.A5, R31.2
unnamed: D14.A, R32.2
unnamed: JP3.1, R32.1
unnamed: D15.DO, TP10.P$1
unnamed: R36.2, U22.5
unnamed: D17.A, R40.2
unnamed: J14.B5, R42.2
unnamed: J14.A5, R43.2
unnamed: D19.A, R44.2
unnamed: JP4.1, R44.1
unnamed: D20.DO, TP14.P$1
unnamed: R47.2, U29.5
unnamed: D22.A, R51.2
unnamed: D12.A, R34.2
unnamed: J18.B5, R53.2
unnamed: J18.A5, R54.2
unnamed: D24.A, R55.2
unnamed: JP5.1, R55.1
unnamed: D25.DO, TP18.P$1
unnamed: R58.2, U36.5
unnamed: D27.A, R62.2
unnamed: J22.B5, R64.2
unnamed: J22.A5, R65.2
unnamed: D29.A, R66.2
unnamed: JP6.1, R66.1
unnamed: D30.DO, TP22.P$1
unnamed: R69.2, U43.5
unnamed: D32.A, R73.2
unnamed: J26.B5, R75.2
unnamed: J26.A5, R76.2
unnamed: D34.A, R77.2
unnamed: JP7.1, R77.1
unnamed: D35.DO, TP26.P$1
unnamed: R80.2, U50.5
unnamed: D37.A, R84.2
unnamed: J30.B5, R86.2
unnamed: J30.A5, R87.2
unnamed: D39.A, R88.2
unnamed: JP8.1, R88.1
unnamed: D40.DO, TP30.P$1
unnamed: R91.2, U57.5
unnamed: D42.A, R95.2
unnamed: J34.B5, R97.2
unnamed: J34.A5, R98.2
unnamed: D44.A, R99.2
unnamed: JP9.1, R99.1
unnamed: D45.DO, TP34.P$1
unnamed: R102.2, U64.5
unnamed: D47.A, R106.2
unnamed: J38.B5, R108.2
unnamed: J38.A5, R109.2
unnamed: D49.A, R110.2
unnamed: JP10.1, R110.1
unnamed: D50.DO, TP38.P$1
QWIIC_PWR: C3.1, J3.2, U5.5
QWIIC_PWR1: C17.1, J2.2, U14.5
QWIIC_PWR2: C28.1, J9.2, U21.5
QWIIC_PWR3: C38.1, J13.2, U28.5
QWIIC_PWR4: C48.1, J17.2, U35.5
QWIIC_PWR5: C58.1, J21.2, U42.5
QWIIC_PWR6: C68.1, J25.2, U49.5
QWIIC_PWR7: C78.1, J29.2, U56.5
QWIIC_PWR8: C88.1, J33.2, U63.5
QWIIC_PWR9: C98.1, J37.2, U70.5
RTS-10K: Q2.2, R18.2
RTS-10K1: Q1.2, R13.2
RTS-10K2: Q5.2, R26.2
RTS-10K3: Q7.2, R38.2
RTS-10K4: Q9.2, R49.2
RTS-10K5: Q11.2, R60.2
RTS-10K6: Q13.2, R71.2
RTS-10K7: Q15.2, R82.2
RTS-10K8: Q17.2, R93.2
RTS-10K9: Q19.2, R104.2
TP_EN: R8.2, U3.3, U6.EN
TP_EN1: R16.2, U9.3, U11.EN
TP_EN2: R29.2, U16.3, U18.EN
TP_EN3: R41.2, U23.3, U25.EN
TP_EN4: R52.2, U30.3, U32.EN
TP_EN5: R63.2, U37.3, U39.EN
TP_EN6: R74.2, U44.3, U46.EN
TP_EN7: R85.2, U51.3, U53.EN
TP_EN8: R96.2, U58.3, U60.EN
TP_EN9: R107.2, U65.3, U67.EN
VIN: C7.1, D4.C, Q3.2, R8.1, U3.1, U5.1
VIN1: C8.1, D7.C, Q4.2, R16.1, U9.1, U14.1
VIN2: C21.1, D13.C, Q6.2, R29.1, U16.1, U21.1
VIN3: C31.1, D18.C, Q8.2, R41.1, U23.1, U28.1
VIN4: C41.1, D23.C, Q10.2, R52.1, U30.1, U35.1
VIN5: C51.1, D28.C, Q12.2, R63.1, U37.1, U42.1
VIN6: C61.1, D33.C, Q14.2, R74.1, U44.1, U49.1
VIN7: C71.1, D38.C, Q16.2, R85.1, U51.1, U56.1
VIN8: C81.1, D43.C, Q18.2, R96.1, U58.1, U63.1
VIN9: C91.1, D48.C, Q20.2, R107.1, U65.1, U70.1
V_BATT: C6.1, C15.1, J4.2, Q3.3, U1.3, U4.2, U4.3, U6.V_BATT
V_BATT1: C11.1, C16.1, J8.2, Q4.3, U8.3, U11.V_BATT, U13.2, U13.3
V_BATT2: C23.1, C27.1, J12.2, Q6.3, U15.3, U18.V_BATT, U20.2, U20.3
V_BATT3: C33.1, C37.1, J16.2, Q8.3, U22.3, U25.V_BATT, U27.2, U27.3
V_BATT4: C43.1, C47.1, J20.2, Q10.3, U29.3, U32.V_BATT, U34.2, U34.3
V_BATT5: C53.1, C57.1, J24.2, Q12.3, U36.3, U39.V_BATT, U41.2, U41.3
V_BATT6: C63.1, C67.1, J28.2, Q14.3, U43.3, U46.V_BATT, U48.2, U48.3
V_BATT7: C73.1, C77.1, J32.2, Q16.3, U50.3, U53.V_BATT, U55.2, U55.3
V_BATT8: C83.1, C87.1, J36.2, Q18.3, U57.3, U60.V_BATT, U62.2, U62.3
V_BATT9: C93.1, C97.1, J40.2, Q20.3, U64.3, U67.V_BATT, U69.2, U69.3
V_USB: C19.1, D4.A, J1.VBUS1, J1.VBUS2, Q3.1, R3.1, R7.2, U1.4, U6.V_USB
V_USB1: C12.1, D7.A, J5.VBUS1, J5.VBUS2, Q4.1, R1.2, R5.1, U8.4, U11.V_USB
V_USB2: C24.1, D13.A, J10.VBUS1, J10.VBUS2, Q6.1, R22.2, R23.1, U15.4, U18.V_USB
V_USB3: C34.1, D18.A, J14.VBUS1, J14.VBUS2, Q8.1, R33.2, R35.1, U22.4, U25.V_USB
V_USB4: C44.1, D23.A, J18.VBUS1, J18.VBUS2, Q10.1, R45.2, R46.1, U29.4, U32.V_USB
V_USB5: C54.1, D28.A, J22.VBUS1, J22.VBUS2, Q12.1, R56.2, R57.1, U36.4, U39.V_USB
V_USB6: C64.1, D33.A, J26.VBUS1, J26.VBUS2, Q14.1, R67.2, R68.1, U43.4, U46.V_USB
V_USB7: C74.1, D38.A, J30.VBUS1, J30.VBUS2, Q16.1, R78.2, R79.1, U50.4, U53.V_USB
V_USB8: C84.1, D43.A, J34.VBUS1, J34.VBUS2, Q18.1, R89.2, R90.1, U57.4, U60.V_USB
V_USB9: C94.1, D48.A, J38.VBUS1, J38.VBUS2, Q20.1, R100.2, R101.1, U64.4, U67.V_USB

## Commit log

2021-02-16 Add production files
2021-04-28 Add test sketches
2021-04-28 Add programming tools
2021-05-10 Update file names
2021-12-26 Add Library Manager helper link for FastLED
